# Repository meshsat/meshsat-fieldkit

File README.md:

# MeshSat Field Kit hardware

Hardware for the MeshSat field kits, the portable go-boxes that carry a MeshSat Bridge (a Raspberry Pi 5 in V1, three Compute Module 5 in V2) with its radios, satellite modem, cellular modem, GPS and power into the field. Since October 2026 it also holds the compact kit, the pocket-sized node (`compact/`). The software lives in the [meshsat](https://github.com/meshsat/meshsat) repository. This repository holds the mechanical and electronic design, the build records and the manufacturing files.

MeshSat is a prototype. Nothing here has been through a field deployment yet. The V1 kits are bench and demo units. The V2 boards are designed and generated, and the engineering foundations beneath them are still being completed: no V2 board is ready for layout, no layout of boards A, B, C, D, E or P carries its board's corrected schematic (E5 has none), and none has been fabricated or ordered ([`v2/docs/CURRENT-EVIDENCE.md`](v2/docs/CURRENT-EVIDENCE.md): "Foundations incomplete; 0 boards ready for layout; 0 physically verified").

## Latest: compact v2, the pocket-sized node in a printed enclosure (6 October 2026)

<sub>The compact v2 enclosure exploded, as designed (an OpenSCAD render; nothing printed). From the bottom: the belt plate, the body with the SOS guard and the LoRa antenna, the RockBLOCK 9704-SMA on its rails, the printed separator, the T-Beam Supreme with its 18650 cell, the lid with the OLED window; to the side, the TPU button membrane, the three plungers and their retainer.</sub>

The compact kit is the small MeshSat node: a Meshtastic LoRa radio and an Iridium modem in a case that fits a pocket, running the MeshSat fork of the Meshtastic firmware and talking to the MeshSat phone apps over one Bluetooth link. Its third version, **compact v2**, puts a LILYGO T-Beam Supreme over a RockBLOCK 9704-SMA in a 3D-printed stacked enclosure: ASA body, lid, separator and carry plates, a TPU membrane over the board's three side buttons, an O-ring cord seal, a polycarbonate pane over the OLED, two SMA bulkheads, an IP67 panel USB-C, an M12 vent and a 12 mm IP67 switch under a guard; 62.5 x 146.0 x 62.7 mm, 154.0 mm long with the SOS guard. The design is `meshsat-enclosure` v0.6 of 5 October 2026, the answer to an engineering audit of its v0.5: both boards are registered from the makers' STEP models, every printed part is clash-checked against them, and three test coupons (the 9704 rail slot, the rim with its seal and inserts, the upper bay with the real board) come before any full print. [`compact/`](compact/README.md) holds the version table for compact v0, v1 and v2; [`compact/v2/`](compact/v2/README.md) the source, the print files, the coupons, the renders and the validation chain.

State: designed, and cleared by its own audit response for prototype printing only. The first test coupons are being printed in October 2026; nothing has been printed, fitted or sealed. Open before a full build: the panel part numbers, how the 9704 is powered, Ground Control's certification condition on other transmitters in the same housing, and the leak, button and insert tests ([`compact/v2/AUDIT-RESPONSE.md`](compact/v2/AUDIT-RESPONSE.md)). Firmware, wiring and the Bluetooth contract: [meshsat-esp32](https://github.com/meshsat/meshsat-esp32), [meshsat-firmware](https://github.com/meshsat/meshsat-firmware) and [docs.meshsat.net/node/](https://docs.meshsat.net/node/).

## News

| Date | What |
|---|---|
| 6 October 2026 | The compact kit joins this repository as [`compact/`](compact/README.md): the version table for compact v0, v1 and v2, and the v2 enclosure package (OpenSCAD source, print STLs, test coupons, renders, validation chain, the makers' reference CAD). The first test coupons are being printed. |
| 5 October 2026 | The v2 enclosure reaches v0.6, the response to an engineering audit of v0.5 (findings F01 to F15, [`compact/v2/AUDIT-RESPONSE.md`](compact/v2/AUDIT-RESPONSE.md)): boards registered from the makers' STEP models, every printed part clash-checked, grounded test coupons in place of a floating fit check, a membrane and guided plungers for the side buttons. |
| 4 October 2026 | The V2 programme adopts an execution constitution ([`v2/docs/EXECUTION-CONSTITUTION.md`](v2/docs/EXECUTION-CONSTITUTION.md)): layer deliverables with explicit dependencies, independent checking, one freeze per candidate, and separate statements of handover readiness, power-design closure and fabrication release. |
| 3 October 2026 | A panel controller firmware for board C ([`v2/firmware/panel/`](v2/firmware/panel/README.md)): a portable core with its hardware layer, a pico-sdk port and host tests. The supplier engineering-handover entry page ([`v2/docs/handover/supplier/`](v2/docs/handover/supplier/)) with a per-board BOM reader from the committed netlists. Desk work: no board exists. |
| 27 September 2026 | The case set for the Peli 1450 ([`v2/release/case-2026-09-27/`](v2/release/case-2026-09-27/README.md)): face plate, RF entry plates, connector plate, frame legs and the lid tray as CAD, drawings and 1:1 templates. Nothing cut or fitted. |
| 26 September 2026 | Circuit corrections in the schematics of boards A, B, C, D, E and P. No committed layout carries them; the deliverable folders of `v2/release/revA/` predate them. |
| 7 September 2026 | The MESHSAT-830 generation: the Peli 1450 go-box around three Compute Module 5 slots, its boards generated from their generators (the V2 section below). |
| 3 September 2026 | This repository opens with the Rev A design release (`revA`) of the previous board generation (one compute module, the Touch Display, a twelve-cell battery module), kept on the GitHub release as the record. |
| April 2026 | The V1 kits tesseract and parallax built, in use since as bench and demo units ([`v1/`](v1/README.md)). |

## Folders

| Folder | What it is | State |
|---|---|---|
| `v1/` | tesseract and parallax as built: IP67 case, HDPE plates on M3 rods, UV-K5 + AIOC APRS chain, per-kit BOM and GPIO pinouts, FreeCAD plate model | built April 2026, in use |
| `v2/` | the Peli 1450 go-box of the MESHSAT-830 generation: seven carrier PCBs around three Compute Module 5 slots, an aluminium control face on the 1450PF panel frame with a sealed monitor in it and a backer board under it, a removable stack on a floor dock, a 4S pack built for the kit (about 145 Wh) in the east pocket | first generated 7 September 2026; circuits corrected on 26 September 2026 in the schematics only; foundations incomplete, 0 boards ready for layout, nothing built or ordered |
| `compact/` | the compact kit, the pocket-sized node: the version table for v0 (XIAO ESP32-S3 + Wio-SX1262 + RockBLOCK 9603 bench unit), v1 (LILYGO T-Beam Supreme + RockBLOCK 9603 for a Peli 1020) and v2 (T-Beam Supreme over a RockBLOCK 9704-SMA in a 3D-printed stacked enclosure, OpenSCAD, in `compact/v2/`) | v0 and v1 are bench units running since September 2026 (the v1 Peli build is not finished); v2 designed 5 October 2026, cleared by its own audit response for prototype printing only, nothing printed or fitted |

## V1: tesseract and parallax

Two hand-built kits that differ only in the satellite modem (tesseract: RockBLOCK 9603 SBD, parallax: RockBLOCK 9704 IMT). Pi 5 with a Geekworm X1202 UPS, LilyGO T-Call A7670E, u-blox GPS, Quansheng UV-K5(8) with an AIOC for APRS, ESP32-S3 LoRa for Meshtastic, RTL-SDR v4, ZigBee CC2652P, DCF77 receiver, WeAct 3.7 inch e-paper, Raspberry Pi Touch Display 2, all on three HDPE plates in an IP67 case with SMA bulkheads. Details, BOM and pinouts in [`v1/README.md`](v1/README.md). **To build one: [`v1/BUILD.md`](v1/BUILD.md)** (parts, case drilling, plates, harness tables, software provisioning, checks).

## V2: the carrier set (MESHSAT-830 generation, 7 September 2026)

Seven KiCad 9 boards replace the plates, the loose wiring and the USB hub. Three Raspberry Pi Compute Module 5 sit in identical slots on one carrier, each with a PCIe switch, an NVMe drive, a USB 3 hub and a card slot; most radios and the sensor and panel controllers are USB devices on those hubs, shared by the HAL across the three modules, which run k3s; each of the three hub banks is designed to switch in hardware from its home module to a neighbour, decided by three I/O supervisors voting two of three, so losing a module is meant to move its USB peripherals instead of removing them. Not everything is on a hub: the two WiFi link cards are PCIe cards on two different modules, and only their antennas move; the compute modules' own WiFi and Bluetooth stay with each module; and two bearers have no second path and go with their module, the LoRa module on one module's SPI and the 5G data path on another's PCIe lane ([`v2/docs/ARCH-PCB-B-IOHA.md`](v2/docs/ARCH-PCB-B-IOHA.md) section 15). The stack (PCB-A power with the VHF mezzanine, PCB-B compute) lifts straight out of the case, and a dock strip on the case floor carries the 9 to 36 V front end, the solar tracker, the sensor controller and the contact block that the stack lands on; as generated, eleven antenna paths blind-mate at the same time (a twelfth, the third 5G jack, waits on the board E clamp fit under owner ruling D-07). The face is a 3 mm aluminium plate on the Peli 1450PF frame (over Peli's o-ring, case choice C1) with a Xenarc IP67 monitor set into it, a wide-temperature e-paper under a lens, sealed switches, two headset jacks and a camera window, with the backer board C7 (an RP2040 panel controller) under it and the 30 W VHF amplifier bolted to its underside. The pack is a 4S lithium-ion pack, built rather than bought, for the pocket beside A24 at the east wall (the BB-2590/U did not fit the case; appendix 32.62). On 26 September 2026 the owner ruled its size: one 4S3P block of Samsung INR18650-35E cells, about 145 Wh, shrink-wrapped in that pocket, its fit designed against Peli's own figures ([`v2/docs/CASE-MARGINS.md`](v2/docs/CASE-MARGINS.md)), with missions longer than the pack relying on vehicle or solar input. The product brief, the concept of operations with its PROVISIONAL runtime per power state, the device set and the qualification plan are in [`v2/docs/PRODUCT-BRIEF.md`](v2/docs/PRODUCT-BRIEF.md), [`v2/docs/CONOPS.md`](v2/docs/CONOPS.md), [`v2/docs/V2-SPEC.md`](v2/docs/V2-SPEC.md) and [`v2/docs/TEST-PLAN.md`](v2/docs/TEST-PLAN.md); none of it has been built. Against Peli's own figures, the antenna entries are twelve gas-discharge arrestors on one RF entry plate per end wall at 59 mm and the wall items share one connector plate between the hinge fairings, choices the design session took under the owner's standing rule of 26 September 2026 ([`v2/docs/CASE-MARGINS.md`](v2/docs/CASE-MARGINS.md) section 4); the case generators carry them since `c351115d` and the current case set, CAD, drawings and 1:1 templates, is [`v2/release/case-2026-09-27/`](v2/release/case-2026-09-27/README.md), while the committed board files and the deliverable folders of `v2/release/revA/` predate it.

| Board | Rev (newest deliverable folder) | Declared phase | Size (mm) | Layers | Role |
|---|---|---|---|---|---|
| PCB-A POWER + I/O | A24 | A32 | 240 x 160 | 6 | the 14.4 V node from the 4S pack, BQ25731 SMBus charger, three 5.1 V slot rails and a device rail, the 13.8 V amplifier rail and the 12 V HF rail (both EMCON gated), the 54 V PoE rail, the 45 W USB-C outlet, INA226 rail monitors, the D8 mezzanine site, eleven blind-mate RF receptacles, the dock contacts |
| PCB-B COMPUTE | B19 (quote only, not routed) | B21 | 330 x 200 | 6 (an 8-layer trial ruled 25 Sep 2026) | three Compute Module 5 slots on board-to-board receptacles, per slot a PCIe switch with an NVMe 2242 and a card slot (a WiFi link card, the 5G module, the second WiFi link card), a four-port USB 3 hub and a cooler fan; the KSZ9897 Ethernet switch to the wall port with PoE, the three-input HDMI switch to the monitor, the LimeSDR bay, the RockBLOCK site, the LG290P GNSS, the E22 1 W LoRa module, two E72 radios (Zigbee and Thread), the holdover clock, the secure element, the panel ribbon |
| PCB-C PANEL BACKER | C24 | C24 | 344 x 228 ring | 4 (6 ruled 25 Sep 2026, not yet regenerated) | the ring under the face plate: the RP2040 panel controller (a USB device with the hardware EMCON and ZEROIZE lines), the sixteen LEDs under IP68 light guides (and, in the schematic since its round 8, a seventeenth, the hardware EMCON lamp, whose light guide in the plate is owed), two GPIO expanders, the e-paper flex socket and its boost stage, the sounder driver, the ambient light sensor, the lands for the sealed switches, the holes for the headset jacks and the monitor's connector block |
| PCB-D VHF APRS | D11 | D12 | 100 x 80 | 4 | the NiceRF SA868 exciter, the T/R relay, the low-pass filter and the leads to the RA30H1317M1 30 W module on the plate, a USB audio codec and headphone amplifier for the two headset jacks, a USB hub and the control bridge, the PTT and EMCON logic, the amplifier gate bias switch |
| PCB-E1 DOCK STRIP | E9 | E17 | 267 x 68 | 4 | the floor strip: 9 to 36 V vehicle and shore entry with the LM5176 front end, the solar tracker, the pack entry with its fuse and SMBus, the sensor controller (a second RP2040) with the climate, seal, water, gas, motion, lightning, Geiger and outside-pod inputs, two mixer fans, one blind-mate clamp bar with twelve cavities (board A's eleven RF sites and the third 5G jack of owner ruling D-07), the raised contact block |
| PCB-E5 DOCK BLOCK | E5 | E5 (no schematic) | 43 x 26 | 2 | the raised block on the strip: the targets the stack's spring pins land on, wire lands underneath |
| PCB-P PACK BMS | P4 | P4 | 70 x 44 | 2 (4 at 2 oz ruled 25 Sep 2026, not yet regenerated) | inside the 4S pack: the BQ4050 SMBus gauge with protection and balancing, two high-side N-FETs, the 2 mohm shunt, the 25 A blade, the cell tap, thermistor and SMBus headers, the lead lands (appendix 32.62) |

The revision column names the newest deliverable folder in `v2/release/revA/boards/`, and the declared phase is the board this project is building ([`v2/docs/CURRENT-EVIDENCE.md`](v2/docs/CURRENT-EVIDENCE.md)). Every deliverable folder predates the circuit corrections of 26 September 2026 (`faf8c981`, `458b2873`, `d90f30e4`) and every later one, which are in the schematics only: no layout of boards A, B, C, D, E or P carries its board's corrected netlist (E5 has no schematic). The renders below show those older layouts.

**Reading this page inside an engineering handover snapshot** (`v2/release/handover/<version>.zip`): the snapshot leaves out `v2/images/` (renders, presentation) and `v1/` (the V1 kits, out of the V2 handover's scope), so the images below and the links into `v1/` do not resolve there; they do in this repository. The snapshot's `EXCLUDED.tsv` lists every file left out, and its `START-HERE.md` section 7 says why.

| | |
|---|---|
|  |  |
| PCB-A POWER + I/O | PCB-B COMPUTE |
|  |  |
| PCB-C PANEL BACKER | PCB-D VHF APRS |
|  |  |
| PCB-E1 DOCK STRIP | PCB-E5 DOCK BLOCK |
|  | |
| PCB-P PACK BMS | |

Concept renders of the assembled kit as designed (not built; `v2/cad/render/` holds the Blender scene, `v2/images/concept-1450/README.md` the full set):

| | |
|---|---|
|  |  |
| the open case from the front | the face from above |
|  |  |
| the front wall cut away and the face lifted | the stack without the face |
|  |  |
| the switch corner | closed for transport |

**The V2 build guide, [`v2/BUILD.md`](v2/BUILD.md), is the 7 September generation's guide, kept as the assembly narrative and not to be used to order boards:** no board is ready for layout, and the order folder is rebuilt and quarantined with nothing ordered from it (owner decision 41 of 25 September 2026). Sources, generators, vendor references, the release and the order record are described in [`v2/README.md`](v2/README.md). The design record is [`v2/docs/MESHSAT-709-geometry-appendix.md`](v2/docs/MESHSAT-709-geometry-appendix.md), the build procedure [`v2/docs/ASSEMBLY.md`](v2/docs/ASSEMBLY.md), the panel controller contract [`v2/docs/PANEL.md`](v2/docs/PANEL.md).

## How to build one

| | Guide | What it covers |
|---|---|---|
| V1 | [`v1/BUILD.md`](v1/BUILD.md) | the 33-line parts list per kit, bulkhead and hole schedule, the three HDPE plates and the rod stack, what goes on which floor, the GPIO harness tables for both kits as wired, the Pi 5 provisioning sequence and its traps, the checks that prove the kit works |
| V2 | [`v2/BUILD.md`](v2/BUILD.md) | the 7 September generation's guide, headed as history and not for ordering (decision 41; 0 boards ready for layout): the boards as generated, everything else to buy, case and frame preparation, the 4S pack, the assembly order with torques, leads and pigtails, coating and labels, software bring-up, the open items, with the lines that contradict the current baseline corrected in place |

## Working with this repository

- Binaries (STEP, FreeCAD, DXF, zips, PDFs, renders) are ordinary git objects; a clone is about 400 MB and needs no Git LFS.
- KiCad 9, Freerouting and the generator scripts run headless on a rented build host; see `v2/README.md` for the pipeline and the prerequisites.
- `v2/vendor/` holds third-party reference material (manufacturer CAD, datasheets) under the vendors' own terms; see `v2/vendor/README.md`.

## Mission and use policy

MeshSat does not work with any organisation that develops, produces, integrates or operates weapon systems, and provides nothing for use in one. The licence below is unchanged: the policy covers whom we work with, not what you may do with the code. Read the [MeshSat Mission and Use Policy](https://meshsat.net/policy/).

## Licence

The hardware design, documentation and generator scripts in this repository are released under the CERN Open Hardware Licence Version 2, Strongly Reciprocal (CERN-OHL-S-2.0), see [`LICENSE`](LICENSE). Third-party files under `v2/vendor/` are not covered by it.

## Links

- Project site: [meshsat.net](https://meshsat.net)
- Bridge software: [github.com/meshsat/meshsat](https://github.com/meshsat/meshsat)
- This repository on GitHub: [github.com/meshsat/meshsat-fieldkit](https://github.com/meshsat/meshsat-fieldkit) (mirror of the GitLab original)

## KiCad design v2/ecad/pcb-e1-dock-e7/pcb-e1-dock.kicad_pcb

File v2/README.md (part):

# V2: the Peli 1450 carrier set (MESHSAT-830 generation)

Seven KiCad 9 boards for the kit V2 go-box: a Peli 1450 case with the 1450PF panel frame. The power and compute boards stack on four M3 rods and lift out of the case in one piece; a dock strip on the case floor carries the 9 to 36 V front end, the solar tracker, the sensor controller and the raised contact block that the stack blind-mates onto, with eleven antenna paths mating at the same time as generated (twelve with the third 5G jack of owner ruling D-07, which waits on the board E clamp fit). The control face is a 3 mm aluminium plate on top of the frame, over Peli's o-ring and screwed into Peli's inserts (`cad/face_plate.py`, `release/case-2026-09-27/face-plate/`; the session's case choice C1 of `docs/CASE-MARGINS.md` section 4, which the case generators carry since `c351115d`) with a Xenarc 709GNK monitor set into it, its glass level with the aluminium face (owner ruling of 9 September 2026, appendix 32.85), the backer board C7 hanging under it and the 30 W VHF module bolted to its underside; the 4S pack, built for the kit rather than bought (one 4S3P block of about 145 Wh by the owner's ruling of 26 September 2026, its fit designed against Peli's own figures, `docs/CASE-MARGINS.md`), lies in the pocket at the east end wall (appendix 32.62), and the antenna entries are twelve gas-discharge arrestors on one RF entry plate per end wall at 59 mm (case choices C2 and C4, carried by the case generators and the case set `release/case-2026-09-27/` since `c351115d`; the committed board files and the deliverable folders of `release/revA/` predate them). Nothing here has been built: the boards are designed and generated, no board is ready for layout (`docs/CURRENT-EVIDENCE.md`: "Foundations incomplete; 0 boards ready for layout; 0 physically verified"), and no set has been ordered.

The rulings that bind the design (details in `docs/MESHSAT-709-geometry-appendix.md`, sections 32.49 to 32.61, and the specification `docs/V2-SPEC.md`): three identical Compute Module 5 slots with most radios and the sensor and panel controllers USB devices shared by the HAL, k3s across the modules, and each hub bank switchable in hardware between its home module and a neighbour so one module's loss is meant to move its USB peripherals rather than remove them; the two WiFi link cards are PCIe cards on two modules whose antennas, not the cards, move, the compute modules' own radios stay with each module, and the LoRa module (one module's SPI) and the 5G data path (another's PCIe lane) have no second path and go with their module (`docs/ARCH-PCB-B-IOHA.md` section 15); the pack, the charger and the power control on PCB-A; no vent opening anywhere in the case; EMCON a hardware line from the panel toggle, plus a software hold, meant to silence every transmitter, with the radios dark and only the VHF receiver, GNSS, DCF77 and the lightning sensor still listening (the owner's ruling of 26 September 2026): as generated at `45bde541` it is drawn to remove the supply of the SDR, the RockBLOCK, the LoRa module, both Zigbee and Thread radios, the HF unit and both WiFi link cards, to turn off the amplifier's rail and keying while the VHF exciter keeps receiving, to pull the compute modules' own WiFi and Bluetooth disables low, and to put the 5G module in airplane mode through its disable pin, and since board B's round 8 (27 September 2026) it also removes the 5G module's supply by hardware at once (SD-EMC-1r8; `docs/CONOPS.md` section 4b, `docs/feasibility/EMCON.md` section 4b); read transmitter by transmitter (`docs/feasibility/EMCON.md` section 0a) none of the kit's 17 transmitters is dark end to end: the radio's own chain closes at desk for 15 and is open for the SA868 (its PTT pin's receive threshold is unpublished) and the RockBLOCK 9704 (once its supply is cut it runs on its own supercapacitors with its ENABLE held by firmware, so the ENABLE forced low by the EMCON hardware is owed); every row also waits on the items the rows share (the toggle and its conductor, whose hardware EMCON lamp is drawn on board C since its round 8 with its light guide in the plate owed) and on the latency the session set (1 s, 20 s for a running 5G module; REQ-071), and no row has been shown on a bench (feasibility blocker FEA-002); the panel a USB device driven per `docs/PANEL.md`.

| Board | Rev (newest deliverable folder) | Declared phase | Size (mm) | Layers | Project | Deliverable folder |
|---|---|---|---|---|---|---|
| PCB-A POWER + I/O | A24 | A32 | 240 x 160 | 6 | `ecad/pcb-a-power-a23/` | `release/revA/boards/meshsat-pcb-a-revA-A24/` |
| PCB-B COMPUTE | B19 | B21 | 330 x 200 | 6 (8-layer trial ruled 25 Sep 2026) | `ecad/pcb-b-compute-b19/` | `release/revA/boards/meshsat-pcb-b-revA-B19-quote/` (quote only: placed, not routed) |
| PCB-C PANEL BACKER | C24 | C24 | 344 x 228 ring | 4 (6 ruled 25 Sep 2026, not yet regenerated) | `ecad/pcb-c-display-c8/` | `release/revA/boards/meshsat-pcb-c-revA-C24/` |
| PCB-D VHF APRS | D11 | D12 | 100 x 80 | 4 | `ecad/pcb-d-aprs-d9/` | `release/revA/boards/meshsat-pcb-d-revA-D11/` |
| PCB-E1 DOCK STRIP | E9 | E17 | 267 x 68 | 4 | `ecad/pcb-e1-dock-e7/` | `release/revA/boards/meshsat-pcb-e-revA-E9/` |
| PCB-E5 DOCK BLOCK | E5 | E5 (no schematic) | 43 x 26 | 2 | `ecad/pcb-e5-block/` | `release/revA/boards/meshsat-pcb-e5-revA-E5/` |
| PCB-P PACK BMS | P4 | P4 | 70 x 44 | 2 (2 oz; 4 at 2 oz ruled 25 Sep 2026, not yet regenerated) | `ecad/pcb-p-pack-p2/` | `release/revA/boards/meshsat-pcb-p-revA-P4/` |

Every deliverable folder in this table predates the circuit corrections of 26 September 2026 (`faf8c981`, `458b2873`, `d90f30e4`) and every later one, which are in the schematics only: no layout of boards A, B, C, D, E or P carries its board's corrected netlist (SCH-002 reads FAIL on A and B and INCONCLUSIVE on C, D, E and P; E5 has no schematic, and its board file is its design), and each board's remaining layout-entry blockers are listed in `docs/CURRENT-EVIDENCE.md`.

The previous generation (A21, B15, C6, D7, E4, E5 with a single Compute Module, the Touch Display and a twelve-cell battery module) stays on the `revA` GitHub release and in the git history as the record; its deliverable folders are replaced as the new boards land.

**Build guide: [`BUILD.md`](BUILD.md)** is the 7 September generation's guide, kept as the assembly narrative and headed as not for ordering (owner decision 41; no board is ready for layout). This page is the map of the folder.

## Layout

| Path | Content |
|---|---|
| `docs/` | `MESHSAT-709-geometry-appendix.md` (the design record, every number and every ruling), `ASSEMBLY.md` (fasteners, torque, coating, removal procedure, bench-fit lists), `PANEL.md` (the software contract for the control panel, MESHSAT-773), `V2-SPEC.md` (the approved specification of the next generation, MESHSAT-830, with its corrections of 26 September 2026), `TEST-PLAN.md` (its qualification plan), `PRODUCT-BRIEF.md` and `CONOPS.md` (the product brief and the concept of operations of the foundation baseline, MESHSAT-1357), `CURRENT-EVIDENCE.md` (what each board's evidence shows today), `CASE-MARGINS.md` (the case held against Peli's own figures, with the case choices C1 to C6), `ARCHITECTURE.md` and `feasibility/` (the architecture and the feasibility of the core functions), `EXECUTION-PLAN.md` (the foundation programme and its stage gates), `records/` (the session records the pages cite) and `reviews/` (the owner's reviews and prompts) |
| `ecad/` | the KiCad sources: one project folder per board, `meshsat.pretty/` (project footprints), `tools/` (the generators and the pipeline scripts) |
| `vendor/` | third-party reference CAD and datasheets (see `vendor/README.md`) |
| `release/revA/boards/` | the Rev A deliverables: KiCad project snapshot, Gerber zip, BOM, CPL, DRC report, schematic PDF, renders, 1:1 print |
| `release/revA/order/` | the JLCPCB order set: per-board upload folder with `ORDER-NOTES.txt`, `ORDER-LOG.md` (what was uploaded and what JLCPCB answered), `jlc-rotations.csv` and `jlc_final.py` (the rotation fixes applied to the CPL) |
| `release/revA/review/` | the review prints: 1:1 sheets, assembly drawings, copper layers, schematics, renders at A4 |
| `images/` | downscaled top renders for the README (left out of the engineering handover snapshots under `release/handover/`, as presentation, so the README's image links do not resolve inside a snapshot; they do in this repository) |

## State of the MESHSAT-830 generation

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
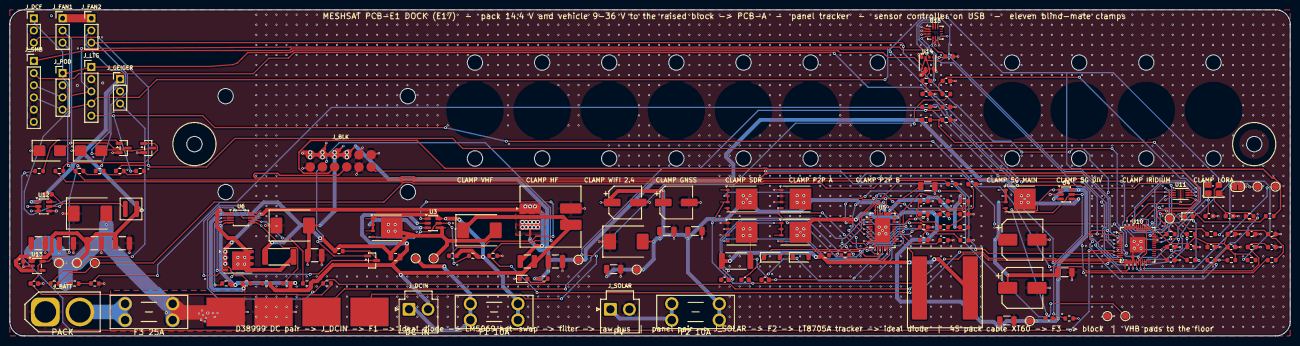
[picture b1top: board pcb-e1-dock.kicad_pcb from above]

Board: 4 copper layers, 267.0 x 68.0 mm, 189 parts (0 on the bottom side), 94 nets.

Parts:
C1, C31: 10u 25V 1210; C_1210_3225Metric
C2: 100n 100V; C_0805_2012Metric
C4, C28: 100n 50V; C_0603_1608Metric
C5: 100n (TIMER); C_0603_1608Metric
C6: 1u 100V 1210 (X, input side); C_1210_3225Metric
C7: 1u 100V 1210 (X, bus side); C_1210_3225Metric
C8: 10u 100V X7R 1210; C_1210_3225Metric
C11, C12: 100u 35V Panasonic EEHZK1V101XP hybrid polymer (7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; CP_Elec_6.3x7.7
C13, C14: 10u 50V; C_1206_3216Metric
C15: 4.7u 50V; C_1206_3216Metric
C16: 1n; C_0603_1608Metric
C17, C18: 470n 25V; C_0603_1608Metric
C19: 4.7u 25V; C_1206_3216Metric
C20, C34, C35, C45, C46, C47: 1u; C_0603_1608Metric
C21: 4.7n; C_0603_1608Metric
C22: 100p; C_0603_1608Metric
C23, C30, C38, C39, C40, C41, C42, C43, C44, C48, C49, C50, C51: 100n; C_0603_1608Metric
C24, C25: 39u 35V Panasonic 35SVPF39M polymer (6.9 mm); CP_Elec_8x6.7
C26, C27: 10u 25V; C_1206_3216Metric
C32, C33: 22u 10V X7R 1210; C_1210_3225Metric
C36, C37: 15p; C_0603_1608Metric
D1: SMCJ40A (input surge: 40 V standoff on a line spe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; D_SMC
D2: SMCJ40A (bus clamp: 40 V standoff on the 9 to 36 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; D_SMC
D3: SMCJ18A (pack node clamp); D_SMC
D4: SMCJ28A (panel surge: 28 V standoff, conducting f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; D_SMC
D5: BAT54 boost diode INTVCC -> BOOST1; D_SOD-123
D6: BAT54 boost diode INTVCC -> BOOST2; D_SOD-123
D7: SS14 flyback across fan 1; D_SMB
D8: SS14 flyback across fan 2; D_SMB
F1: 10 A mini blade (Keystone 3568 holder): vehicle i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; Fuseholder_Blade_Mini_Keystone_3568
F2: 10 A mini blade (Keystone 3568 holder): panel inp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; Fuseholder_Blade_Mini_Keystone_3568
F3: 25 A mini blade (Keystone 3568 holder): pack to t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; Fuseholder_Blade_Mini_Keystone_3568
H1, H2: M3 rod pass-through, PCB-A standoff stands here; MountingHole_3.2mm_M3
H3, H4, H5, H6: M3 standoff, raised block; MountingHole_3.2mm_M3
H7, H8: M3, float clamp VHF; MountingHole_3.2mm_M3
H9, H10: M3, float clamp HF; MountingHole_3.2mm_M3
H11, H12: M3, float clamp WIFI 2.4; MountingHole_3.2mm_M3
H13, H14: M3, float clamp GNSS; MountingHole_3.2mm_M3
H15, H16: M3, float clamp SDR; MountingHole_3.2mm_M3
H17, H18: M3, float clamp P2P A; MountingHole_3.2mm_M3
H19, H20: M3, float clamp P2P B; MountingHole_3.2mm_M3
H21, H22: M3, float clamp 5G MAIN; MountingHole_3.2mm_M3
H23, H24: M3, float clamp 5G DIV; MountingHole_3.2mm_M3
H25, H26: M3, float clamp IRIDIUM; MountingHole_3.2mm_M3
H27, H28: M3, float clamp LORA; MountingHole_3.2mm_M3
JP1: BOOTSEL: short while powering to enter the USB bo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; SolderJumper-2_P1.3mm_Open_RoundedPad1.0x1.5mm
J_BATT: Amass XT60-M: the BB-2590/U pack cable BTA-70762-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; AMASS_XT60-M_1x02_P7.20mm_Vertical
J_BLK: solder lands for the 12 signal wires to the block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; PogoTargets_2x6
J_DCF: DCF77 receiver module: 3.3 V, GND, pulse; PinHeader_1x03_P2.54mm_Vertical
J_DCIN: JST-VH socket, 10 A: vehicle and shore DC in 9 to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; JST_VH_B2P-VH_1x02_P3.96mm_Vertical
J_FAN1: mixer fan 1 under the plate (12 V class fan on th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; PinHeader_1x03_P2.54mm_Vertical
J_FAN2: mixer fan 2 under the plate (12 V class fan on th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; PinHeader_1x03_P2.54mm_Vertical
J_GEIGER: Geiger counter module (RadiationD-v1.1 class): 5 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; PinHeader_1x03_P2.54mm_Vertical
J_LTG: AS3935 lightning sensor module (CJMCU-3935 class)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; PinHeader_1x05_P2.54mm_Vertical
J_POD: outside sensor pod on the connector plate (M8 sea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; PinHeader_1x04_P2.54mm_Vertical
J_SMB: pack SMBus (XH or pin header): section A SDA SCL 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; PinHeader_1x06_P2.54mm_Vertical
J_SOLAR: JST-VH socket, 10 A: bare panel in (lead from the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; JST_VH_B2P-VH_1x02_P3.96mm_Vertical
L1: 10uH Coilcraft XAL1510-103MED (Isat 26 A, 10.0 mm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; L_Coilcraft_XAL1510-103
L2: Bourns SRF1260-4R7Y dual-winding choke (7.2 A per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; L_CommonModeChoke_Bourns_SRF1260
L3: 4.7uH XAL4030-472ME; L_Coilcraft_XAL4020-XXX
LED1: green: vehicle input present; LED_0603_1608Metric
LED2: status (GPIO25); LED_0603_1608Metric
PAD_W1: water electrode A (bare copper, +3.3 V through 1 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; SolderPad_8x6
PAD_W2: water electrode B (bare copper, to ADC0); SolderPad_8x6
P_CN: solder pad, 12 AWG wire to the block board return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; SolderPad_8x6
P_CP: solder pad, 12 AWG wire to the block board CELL+ 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; SolderPad_8x6
Q1, Q2: BSC039N06NS 60 V 3.9 mOhm N-FET (PG-TDSON-8: 1-3 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; TDSON-8-1
Q3: BSC028N06NS 60 V 2.8 mOhm N-FET, M1 buck top (TDS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; TDSON-8-1
Q4: BSC039N06NS 60 V N-FET, M2 buck bottom; TDSON-8-1
Q5: BSC028N06NS 60 V N-FET, M3 boost bottom; TDSON-8-1
Q6: BSC039N06NS 60 V N-FET, M4 boost top; TDSON-8-1
Q7: CSD19532Q5B 100 V N-FET (4.6 mOhm at VGS 6 V, Pow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; PowerPAK_SO-8_Single
Q8: 2N7002: SHORE_INHIBIT high pulls UVLO low = input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; SOT-23
Q9: 2N7002 fan 1 low-side switch (1 G, 2 S, 3 D); SOT-23
Q10: 2N7002 fan 2 low-side switch (1 G, 2 S, 3 D); SOT-23
R1, R18, R26: 100k; R_0603_1608Metric
R5: 5 mOhm 1% 3 W 2512 RSENSE (RALEC LR2512-23R005F4); R_2512_6332Metric
R6, R7, R44, R45: 100R; R_0603_1608Metric
R8: 102k 1% (RFBIN1: panel point 17.6 V); R_0603_1608Metric
R9: 7.50k 1% (RFBIN2); R_0603_1608Metric
R10: 115k 1% (RFBOUT1: 15.1 V); R_0603_1608Metric
R11: 10.0k 1% (RFBOUT2); R_0603_1608Metric
R12: 215k 1% (RT: 202 kHz); R_0603_1608Metric
R13, R16, R17, R25, R31, R46, R47, R49, R50: 10k; R_0603_1608Metric
R14, R20, R22, R40, R42: 100k 1%; R_0603_1608Metric
R15: 15.0k 1% (SHDN: enable above about 9.5 V); R_0603_1608Metric
R19: 10mOhm 1% 2512 (hot-swap sense); R_2512_6332Metric
R21: 38.3k 1% (UVLO: 9 V); R_0603_1608Metric
R23: 6.65k 1% (OVLO: 40 V); R_0603_1608Metric
R24: 20k (PWR: power limit); R_0603_1608Metric
R27: 2.2k; R_0603_1608Metric
R28, R33: 1k; R_0603_1608Metric
R29, R30: 27R; R_0603_1608Metric
R32: 1k (BOOTSEL); R_0603_1608Metric
R34, R35, R36, R37: 4.7k; R_0603_1608Metric
R38, R39: 1M; R_0603_1608Metric
R41: 10k 1% (ADC1: 0.091 x bus); R_0603_1608Metric
R43: 22k 1% (ADC2: 0.18 x pack); R_0603_1608Metric
R48: 22R (pulse input series); R_0603_1608Metric
R51: 0R (CSB high: I2C mode; its own net keeps the pin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; R_0603_1608Metric
TP1: DC_IN; TestPoint_Pad_D1.5mm
TP2: DC_P; TestPoint_Pad_D1.5mm
TP3: VIN_RAW; TestPoint_Pad_D1.5mm
TP4: GND; TestPoint_Pad_D1.5mm
TP5: PV_P; TestPoint_Pad_D1.5mm
TP6: TRK_OUT; TestPoint_Pad_D1.5mm
TP7: BLK_SPARE; TestPoint_Pad_D1.5mm
TP8: CELL_F; TestPoint_Pad_D1.5mm
TP9: +5V_E6; TestPoint_Pad_D1.5mm
TP10: SWCLK; TestPoint_Pad_D1.5mm
TP11: SWDIO; TestPoint_Pad_D1.5mm
TP12: E6_RUN; TestPoint_Pad_D1.5mm
TP13: GEIGER_IN; TestPoint_Pad_D1.5mm
U3, U4: LM74700-Q1 ideal-diode controller: 1 VCAP 2 GND 3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; SOT-23-6
U5: LT8705A buck-boost controller, 38-lead QFN 5x7 (p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; WQFN-38-1EP_5x7mm_P0.5mm_EP3.15x5.15mm
U6: LM5069MM-2 hot-swap controller: 9 V on, 40 V off,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; VSSOP-10_3x3mm_P0.5mm
U10: RP2040 sensor controller (USB to B16 through the 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; QFN-56-1EP_7x7mm_P0.4mm_EP3.2x3.2mm
U11: W25Q16JVUXIQ 16 Mbit QSPI flash (USON-8: 1 CS 2 D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; Winbond_USON-8-1EP_3x2mm_P0.5mm_EP0.2x1.6mm
U12: AP63205WU-7 5 V 2 A buck for the controller, the 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; TSOT-23-6
U13: TLV75533PDBVR 3.3 V LDO; SOT-23-5
U14: BME688 inside climate: temperature, humidity, pre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; Bosch_LGA-8_3x3mm_P0.8mm_ClockwisePinNumbering
U15: BMI270 six-axis IMU (I2C 0x68): shock and tilt lo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; Bosch_LGA-14_3x2.5mm_P0.5mm
Y1: 12 MHz ABM8-272-T3 (3225): 1 XIN, 3 XOUT, 2 and 4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; Crystal_SMD_3225-4Pin_3.2x2.5mm

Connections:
/+3V3_E6: C35.1, C38.1, C39.1, C40.1, C41.1, C42.1, C43.1, C44.1, C47.1, C48.1, C49.1, C50.1, J_DCF.1, J_LTG.1, J_POD.1, R25.2, R31.2, R34.2, R35.2, R36.2, R37.2, R38.1, R46.2, R47.2, R49.2, R50.2, R51.1, U10.1, U10.10, U10.22, U10.33, U10.42, U10.43, U10.44, U10.48, U10.49, U11.8, U13.5, U14.2, U14.6, U14.8, U15.5, U15.8
/+5V_E6: C32.1, C33.1, C34.1, J_GEIGER.1, L3.2, TP9.1, U12.1, U13.1, U13.3
/BLK_SPARE: J_BLK.12, TP7.1
/BOOT_J: JP1.1, R32.2
/CELL+: F3.1, J_BATT.2
/CELL_F: C1.1, C31.1, D3.2, D7.1, D8.1, F3.2, J_FAN1.1, J_FAN2.1, P_CP.1, R42.1, TP8.1, U12.2, U12.3
/CELL_MON: R42.2, R43.1, U10.40
/DCF_PULSE: J_DCF.3, R49.1, U10.8
/DCIN_PGD: R25.1, U6.8, U10.15
/DC_F: C4.2, F1.2, Q1.1, Q1.2, Q1.3, R1.2, U3.3, U3.6
/DC_HS: C6.1, L2.1, Q7.1, Q7.2, Q7.3, U6.9
/DC_IN: F1.1, J_DCIN.1, TP1.1
/DC_P: C2.1, D1.2, Q1.5, R19.1, R20.1, R22.1, TP2.1, U3.4, U6.2
/E6_BST: C30.1, U12.6
/E6_DVDD: C45.1, C46.1, U10.23, U10.45, U10.50
/E6_RUN: R31.1, TP12.1, U10.26
/E6_SW: C30.2, L3.1, U12.5
/FAN1_G: Q9.1, R44.2
/FAN1_PWM: R44.1, U10.11
/FAN1_SW: D7.2, J_FAN1.2, Q9.3
/FAN1_TACH: J_FAN1.3, R46.1, U10.13
/FAN2_G: Q10.1, R45.2
/FAN2_PWM: R45.1, U10.12
/FAN2_SW: D8.2, J_FAN2.2, Q10.3
/FAN2_TACH: J_FAN2.3, R47.1, U10.14
/GEIGER_IN: R48.2, TP13.1, U10.9
/GEIGER_PULSE: J_GEIGER.3, R48.1
/GND_V: C2.2, C5.2, C6.2, D1.1, J_DCIN.2, L2.3, Q8.2, R21.2, R23.2, R24.2, U3.2, U6.5
/HS_GATE: Q7.4, U6.10
/HS_OVLO: R22.2, R23.1, U6.4
/HS_PWR: R24.1, U6.7
/HS_S: Q7.5, R19.2, U6.1
/HS_TIMER: C5.1, U6.6
/HS_UVLO: Q8.3, R20.2, R21.1, U6.3
/IMU_CSB: R51.2, U15.12
/IMU_INT1: U10.16, U15.4
/LED_A: LED1.2, R27.2
/LED_STAT: R33.1, U10.37
/LED_STAT_A: LED2.2, R33.2
/LTG_IRQ: J_LTG.5, R50.1, U10.17
/PV_IN: F2.1, J_SOLAR.1
/PV_P: C11.1, C12.1, C13.1, C14.1, C15.1, D4.2, F2.2, Q3.5, R8.1, R14.1, TP5.1, U5.32, U5.33, U5.34
/Q1_G: Q1.4, R1.1, U3.5
/Q2_G: Q2.4, R18.1, U4.5
/QSPI_D0: U10.53, U11.5
/QSPI_D1: U10.55, U11.2
/QSPI_D2: U10.54, U11.3
/QSPI_D3: U10.51, U11.7
/QSPI_SCLK: U10.52, U11.6
/QSPI_SS: R32.1, U10.56, U11.1
/SCL0: J_SMB.2, R35.1, U10.5
/SCL1: J_LTG.4, J_POD.4, J_SMB.4, R37.1, U10.7, U14.4, U15.13
/SDA0: J_SMB.1, R34.1, U10.4
/SDA1: J_LTG.3, J_POD.3, J_SMB.3, R36.1, U10.6, U14.3, U15.14
/SHORE_INHIBIT: J_BLK.8, Q8.1, R26.1, U10.18
/SWCLK: TP10.1, U10.24
/SWDIO: TP11.1, U10.25
/TRK_BG1: Q4.4, U5.14
/TRK_BG2: Q5.4, U5.16
/TRK_BOOST1: C17.1, D5.1, U5.23
/TRK_BOOST2: C18.1, D6.1, U5.17
/TRK_CSN: C16.2, R7.2, U5.2
/TRK_CSP: C16.1, R6.2, U5.3
/TRK_FBIN: R8.2, R9.1, U5.5
/TRK_FBOUT: R10.2, R11.1, U5.6
/TRK_IMONI: R16.1, U5.38
/TRK_IMONO: R17.1, U5.7
/TRK_INTVCC: C19.1, D5.2, D6.2, U5.15, U5.35, U5.36
/TRK_LDO33: C20.1, U5.4
/TRK_LSENSE: L1.2, R5.1, R6.1
/TRK_OUT: C24.1, C25.1, C26.1, C27.1, C28.2, Q2.1, Q2.2, Q2.3, Q6.5, R10.1, R18.2, TP6.1, U4.3, U4.6, U5.29, U5.30, U5.31
/TRK_RT: R12.1, U5.12
/TRK_SHDN: R14.2, R15.1, U5.1
/TRK_SS: C23.1, U5.9
/TRK_SW1: C17.2, L1.1, Q3.1, Q3.2, Q3.3, Q4.5, U5.21
/TRK_SW2: C18.2, Q5.5, Q6.1, Q6.2, Q6.3, R5.2, R7.1, U5.19
/TRK_TG1: Q3.4, U5.22
/TRK_TG2: Q6.4, U5.18
/TRK_VC: C22.1, R13.1, U5.8
/TRK_VCC1: C21.1, R13.2
/U3_VCAP: C4.1, U3.1
/U4_VCAP: C28.1, U4.1
/USB_DM_R: R30.1, U10.46
/USB_DP_R: R29.1, U10.47
/USB_E6_N: J_BLK.10, R30.2
/USB_E6_P: J_BLK.9, R29.2
/VIN_MON: R40.2, R41.1, U10.39
/VIN_RAW: C7.1, C8.1, D2.2, J_BLK.1, J_BLK.2, J_BLK.3, J_BLK.4, L2.2, Q2.5, R27.1, R40.1, TP3.1, U4.4
/WATER_A: PAD_W1.1, R38.2
/WATER_SENSE: C51.1, PAD_W2.1, R39.1, U10.38
/XIN: C36.1, U10.20, Y1.1
/XOUT: C37.1, R28.2, Y1.3
/XOUT_R: R28.1, U10.21
GND: C1.2, C7.2, C8.2, C11.2, C12.2, C13.2, C14.2, C15.2, C19.2, C20.2, C21.2, C22.2, C23.2, C24.2, C25.2, C26.2, C27.2, C31.2, C32.2, C33.2, C34.2, C35.2, C36.2, C37.2, C38.2, C39.2, C40.2, C41.2, C42.2, C43.2, C44.2, C45.2, C46.2, C47.2, C48.2, C49.2, C50.2, C51.2, D2.1, D3.1, D4.1, JP1.2, J_BATT.1, J_BLK.5, J_BLK.6, J_BLK.7, J_BLK.11, J_DCF.2, J_GEIGER.2, J_LTG.2, J_POD.2, J_SMB.5, J_SMB.6, J_SOLAR.2, L2.4, LED1.1, LED2.1, P_CN.1, Q4.1, Q4.2, Q4.3, Q5.1, Q5.2, Q5.3, Q9.2, Q10.2, R9.2, R11.2, R12.2, R15.2, R16.2, R17.2, R26.2, R39.2, R41.2, R43.2, TP4.1, U4.2, U5.11, U5.13, U5.37, U5.39, U10.19, U10.57, U11.4, U11.9, U12.4, U13.2, U14.1, U14.5, U14.7, U15.1, U15.2, U15.3, U15.6, U15.7, Y1.2, Y1.4

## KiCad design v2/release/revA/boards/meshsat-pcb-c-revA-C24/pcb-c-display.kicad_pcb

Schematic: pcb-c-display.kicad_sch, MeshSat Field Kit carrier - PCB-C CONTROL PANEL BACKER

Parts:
BZ1: IP67 panel-mount sounder, 5 V DC continuous, beze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; PanelSounder
C1, C2: 10u; C_0805_2012Metric; LCSC C15850
C3, C4, C14, C15, C16: 1u; C_0603_1608Metric
C5, C6: 15p NP0; C_0402_1005Metric
C7, C8, C9, C10, C11, C12, C13, C25, C29, C38: 100n; C_0603_1608Metric
C17, C18, C26, C27: 100n; C_0603_1608Metric; LCSC C14663
C19, C20, C21, C22, C23, C24: 10n; C_0603_1608Metric; LCSC C57112
C28: 4.7u; C_0805_2012Metric
C30, C31, C32, C33, C34, C35, C36, C37: 1u 25V; C_0603_1608Metric
CAM_H1, CAM_H2: M2 screw of the USB camera module (25 x 25 board,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; MountingHole_2.2mm_M2
D1: 3 mm MWARN red, sunlight viewable; LED_D3.0mm
D2: 3 mm MCAUT amber, sunlight viewable; LED_D3.0mm
D3: 3 mm TX red (RF hazard), sunlight viewable; LED_D3.0mm
D4: 3 mm SOSACT red, sunlight viewable; LED_D3.0mm
D5: 3 mm SAT green, sunlight viewable; LED_D3.0mm
D6: 3 mm MESH green, sunlight viewable; LED_D3.0mm
D7: 3 mm LTE green, sunlight viewable; LED_D3.0mm
D8: 3 mm GPS green, sunlight viewable; LED_D3.0mm
D9: 3 mm SHORE green, sunlight viewable; LED_D3.0mm
D10: 3 mm CHG white, sunlight viewable; LED_D3.0mm
D11: 3 mm MSG white, sunlight viewable; LED_D3.0mm
D12: 3 mm BAT1 amber, sunlight viewable; LED_D3.0mm
D13: 3 mm BAT2 green, sunlight viewable; LED_D3.0mm
D14: 3 mm BAT3 green, sunlight viewable; LED_D3.0mm
D15: 3 mm BAT4 green, sunlight viewable; LED_D3.0mm
D16: 3 mm BAT5 green, sunlight viewable; LED_D3.0mm
D17: BAT54 lamp-test tie; D_SOD-123; LCSC C7502705
D18: status (GPIO25); LED_0603_1608Metric
D19: SS2040FL: EPD_SW -> VGH; D_SOD-123F
D20: SS2040FL: pump clamp; D_SOD-123F
D21: SS2040FL: pump -> VGL; D_SOD-123F
FB1, FB2, FB3, FB4: ferrite 600R; L_0603_1608Metric; LCSC C1002
H1, H2, H3, H4, H5, H6, H7, H8: M3 x 6 into the face plate's self-clinching stand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; BackerScrew_M3_GND
JP1: BOOTSEL: short while powering to enter the USB bo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; SolderJumper-2_P1.3mm_Open_RoundedPad1.0x1.5mm
JP2: PANEL_ID strap (closed = variant B); SolderJumper-2_P1.3mm_Open_RoundedPad1.0x1.5mm
J_EPD: Hirose FH34SRJ-24S-0.5SH ZIF for the E2370KS0C1 f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; Hirose_FH34SRJ-24S
J_HSJ1: U-174/U headset jack 1 (Amphenol Nexus class, dra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; PanelJack_17mm
J_HSJ2: U-174/U headset jack 2 (Amphenol Nexus class, dra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; PanelJack_17mm
J_MAINSW: MAIN button lead to A22 J_MAINSW (XH2.5 at the A2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; LeadLands_1x02
J_PANEL: panel ribbon from B16 J_PANEL (IDC 2x13 SMD, unde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; IDC-Header_2x13_P2.54mm_Vertical_SMD
J_PIJ2: PI button lead: two solder lands on the underside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; LeadLands_1x02
L1: 10uH ATNR4010100MT 0.8 A (the boost inductor); L_APV_ANR4020
Q1: AO3401A P-FET high side; SOT-23; LCSC C15127
Q2, Q3, Q4: 2N7002; SOT-23; LCSC C8545
Q5: AO3401A P-FET: the e-paper's supply switch (EPD_P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; SOT-23; LCSC C15127
Q6: Si2302CDS-T1-GE3 logic-level N-FET (Vishay, SOT-2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; SOT-23; LCSC C10488
R1, R6: 1k; R_0603_1608Metric
R2, R3: 27R; R_0603_1608Metric
R4, R42: 10k; R_0603_1608Metric
R5: 1k (BOOTSEL); R_0603_1608Metric
R7, R8: 2.2k; R_0603_1608Metric
R9, R10, R11, R12, R13, R14, R15, R16: 10k; R_0603_1608Metric; LCSC C25804
R17: 2.2k; R_0603_1608Metric; LCSC C4190
R18: 47R; R_0603_1608Metric; LCSC C23182
R19, R44: 100R; R_0603_1608Metric; LCSC C22775
R20, R38, R45: 100k; R_0603_1608Metric; LCSC C25803
R21, R22, R23, R31, R36, R40: 300R; R_0603_1608Metric; LCSC C23025
R24, R25, R26, R27, R28, R29, R30, R32, R33, R34, R35: 180R; R_0603_1608Metric; LCSC C22828
R37: 1k; R_0603_1608Metric; LCSC C21190
R39, R41: 470R; R_0603_1608Metric; LCSC C23179
R43: 0.47R 1%; R_0603_1608Metric
SW_EMCON: EMCON locking toggle (closed = TX inhibit, a hard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; ToggleBody_SPDT
SW_LIGHT: LIGHTING DAY/NIGHT/BLACKOUT toggle DPDT ON-ON-ON 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; ToggleBody_DPDT
SW_MAIN: MAIN PWR 19 mm momentary, green ring (to A22 J_MA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; PanelSwitch_19mm
SW_PI: PI 16 mm recessed momentary, amber ring (PI_SHDN_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; PanelSwitch_16mm
SW_SOS: SOS locking toggle, maintained (APEM 5636ADKB-2V,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; ToggleBody_SPDT
SW_TEST: TEST/ACK 16 mm momentary, white ring; C&K ATP16-S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; PanelSwitch_16mm
SW_ZERO: ZEROIZE locking toggle, maintained (APEM 5636ADKB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; ToggleBody_SPDT
TP1: SWCLK; TestPoint_Pad_D1.5mm
TP2: SWDIO; TestPoint_Pad_D1.5mm
TP3: C_RUN; TestPoint_Pad_D1.5mm
TP4: LED_RAIL; TestPoint_Pad_D1.5mm
TP5: LED_RAIL_SW; TestPoint_Pad_D1.5mm
TP6: +5V; TestPoint_Pad_D1.5mm
TP7: +3V3; TestPoint_Pad_D1.5mm
TP8: GND; TestPoint_Pad_D1.5mm
TP9: EXP_INT; TestPoint_Pad_D1.5mm
TP10: TX_INHIBIT_n; TestPoint_Pad_D1.5mm
TP11: EMCON_HW; TestPoint_Pad_D1.5mm
TP12: ZEROIZE_HW; TestPoint_Pad_D1.5mm
TP13: SPARE1; TestPoint_Pad_D1.5mm
TP14: SPARE2; TestPoint_Pad_D1.5mm
TP15: SPARE3; TestPoint_Pad_D1.5mm
TP16: SPARE4; TestPoint_Pad_D1.5mm
TP17: SPARE5; TestPoint_Pad_D1.5mm
TP18: SPARE6; TestPoint_Pad_D1.5mm
TP19: SPARE7; TestPoint_Pad_D1.5mm
TP20: SPARE8; TestPoint_Pad_D1.5mm
TP21: SPARE9; TestPoint_Pad_D1.5mm
TP22: SPARE10; TestPoint_Pad_D1.5mm
TP23: SPARE11; TestPoint_Pad_D1.5mm
TP24: SPARE12; TestPoint_Pad_D1.5mm
TP25: EPD_BUSY; TestPoint_Pad_D1.5mm
TP26: EPD_VGH; TestPoint_Pad_D1.5mm
TP27: EPD_VGL; TestPoint_Pad_D1.5mm
TP28: HB1; TestPoint_Pad_D1.5mm
TP29: HB2; TestPoint_Pad_D1.5mm
TP30: HB3; TestPoint_Pad_D1.5mm
TP31: SLOT_EN1; TestPoint_Pad_D1.5mm
TP32: SLOT_EN2; TestPoint_Pad_D1.5mm
TP33: SLOT_EN3; TestPoint_Pad_D1.5mm
TP34: HDMI_SEL1; TestPoint_Pad_D1.5mm
TP35: HDMI_SEL2; TestPoint_Pad_D1.5mm
TP36: PI_SHDN_REQ; TestPoint_Pad_D1.5mm
TP37: PI_KILL; TestPoint_Pad_D1.5mm
TP38: SHORE_INHIBIT; TestPoint_Pad_D1.5mm
TP39: PIJ2_A; TestPoint_Pad_D1.5mm
TP40: PIJ2_B; TestPoint_Pad_D1.5mm
U1: PCA9555PW 0x22: LED sinks, light mode inputs; TSSOP-24_4.4x7.8mm_P0.65mm; LCSC C2864778
U2: PCA9555PW 0x23: LED sinks, the battery bar, lamp 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; TSSOP-24_4.4x7.8mm_P0.65mm; LCSC C2864778
U3: RP2040 panel controller (USB device on B16's slot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; QFN-56-1EP_7x7mm_P0.4mm_EP3.2x3.2mm; LCSC C2040
U4: W25Q16JVUXIQ 16 Mbit QSPI flash (USON-8: 1 CS 2 D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; Winbond_USON-8-1EP_3x2mm_P0.5mm_EP0.2x1.6mm; LCSC C2843335
U5: TLV75533PDBV 3.3 V 500 mA LDO for the controller,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; SOT-23-5
U6, U7, U8, U10, U11: USBLC6-2SC6; SOT-23-6; LCSC C7519
U9: 74LVC1G34 non-inverting buffer (2 A 4 Y): EMCON_H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; SOT-23-5
U_LIGHT: Vishay VEML7700 ambient light sensor (1 SCL 2 VDD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; Vishay_VEML7700; LCSC C504893
Y1: 12 MHz ABM8-272-T3 (3225): 1 XIN, 3 XOUT, 2 and 4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; Crystal_SMD_3225-4Pin_3.2x2.5mm; LCSC C20625731

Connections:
/+3V3: C2.1, C4.1, C7.1, C8.1, C9.1, C10.1, C11.1, C12.1, C13.1, C16.1, C17.1, C18.1, C25.1, C38.1, Q5.2 (S), R4.2, R7.2, R8.2, R9.2, R10.2, R11.2, R12.2, R13.2, R14.2, R16.2, R42.2, TP7.1, U1.2 (A1), U1.24 (VDD), U2.2 (A1), U2.21 (A0), U2.24 (VDD), U3.1 (IOVDD), U3.10 (IOVDD), U3.22 (IOVDD), U3.33 (IOVDD), U3.42 (IOVDD), U3.43 (ADC_AVDD), U3.44 (VREG_VIN), U3.48 (USB_VDD), U3.49 (IOVDD), U4.8 (+3V3), U5.5 (+3V3), U6.5 (VBUS), U7.5 (VBUS), U8.5 (VBUS), U9.5 (+3V3), U10.5 (VBUS), U11.5 (VBUS), U_LIGHT.2 (+3V3)
/+5V: BZ1.2 (-), C1.1, C3.1, J_PANEL.1, J_PANEL.2, SW_LIGHT.2, TP6.1, U5.1 (+5V), U5.3 (+5V)
/BAT1_A: D12.2 (A), R31.2
/BAT1_K: D12.1 (K), U2.7 (IO0_3)
/BAT2_A: D13.2 (A), R32.2
/BAT2_K: D13.1 (K), U2.8 (IO0_4)
/BAT3_A: D14.2 (A), R33.2
/BAT3_K: D14.1 (K), U2.9 (IO0_5)
/BAT4_A: D15.2 (A), R34.2
/BAT4_K: D15.1 (K), U2.10 (IO0_6)
/BAT5_A: D16.2 (A), R35.2
/BAT5_K: D16.1 (K), U2.11 (IO0_7)
/BOOT_J: JP1.1 (A), R5.2
/BZ_K: BZ1.1 (+), Q4.3 (D)
/CHG_A: D10.2 (A), R29.2
/CHG_K: D10.1 (K), U1.7 (IO0_3)
/C_DVDD: C14.1, C15.1, U3.23 (DVDD), U3.45 (VREG_VOUT), U3.50 (DVDD)
/C_RUN: R4.1, TP3.1, U3.26 (RUN)
/EMCON_HW: J_PANEL.8, TP11.1, U3.32 (GPIO21), U9.4 (EMCON_HW)
/EPD_BUSY: J_EPD.9 (BUSY_N), TP25.1, U3.9 (GPIO7)
/EPD_CS: J_EPD.12 (CSB), U3.7 (GPIO5)
/EPD_DC: J_EPD.11 (DC), U3.6 (GPIO4)
/EPD_GDR: J_EPD.2 (GDR), Q6.1 (G)
/EPD_PUMP: C31.2, D20.1 (K), D21.2 (A)
/EPD_PWR_n: Q5.1 (G), R42.1, U3.41 (GPIO29_A3)
/EPD_RESE: J_EPD.3 (RESE), Q6.2 (S), R43.1
/EPD_RST: J_EPD.10 (RST_N), U3.8 (GPIO6)
/EPD_SCL: J_EPD.13 (SCL), U3.4 (GPIO2)
/EPD_SDA: J_EPD.14 (SDA), U3.5 (GPIO3)
/EPD_SW: C31.1, D19.1 (K), L1.2, Q6.3 (D)
/EPD_VCC: C28.1, C29.1, J_EPD.15 (VDDIO), J_EPD.16 (VDD), L1.1, Q5.3 (D)
/EPD_VCOM: C37.1, J_EPD.24 (VCOM)
/EPD_VDDD: C34.1, J_EPD.18 (VDDD)
/EPD_VDH: C35.1, J_EPD.20 (VDH)
/EPD_VDHR: C33.1, J_EPD.5 (VDHR)
/EPD_VDL: C36.1, J_EPD.22 (VDL)
/EPD_VGH: C30.1, D19.2 (A), J_EPD.21 (VGH), TP26.1
/EPD_VGL: C32.1, D21.1 (K), J_EPD.23 (VGL), TP27.1
/EXP_INT: J_PANEL.6, TP9.1, U1.1 (~INT), U2.1 (~INT), U3.36 (GPIO24), U8.3 (I/O2), U8.4 (I/O2)
/GPS_A: D8.2 (A), R27.2
/GPS_K: D8.1 (K), U1.11 (IO0_7)
/HB1: J_PANEL.18, TP28.1, U3.13 (GPIO10)
/HB2: J_PANEL.19, TP29.1, U3.14 (GPIO11)
/HB3: J_PANEL.20, TP30.1, U3.15 (GPIO12)
/HDMI_SEL1: J_PANEL.12, TP34.1, U3.27 (GPIO16)
/HDMI_SEL2: J_PANEL.13, TP35.1, U3.28 (GPIO17)
/LED_RAIL: Q1.3 (D), R21.1, R22.1, R23.1, R24.1, R25.1, R26.1, R27.1, R28.1, R29.1, R30.1, R31.1, R32.1, R33.1, R34.1, R35.1, R36.1, R40.1, R41.1, TP4.1
/LED_RAIL_SW: Q1.2 (S), R15.1, R17.1, R39.1, SW_LIGHT.1, TP5.1
/LED_STAT: R6.1, U3.37 (GPIO25)
/LED_STAT_A: D18.2 (A), R6.2
/LIGHT_DAY_n: C22.1, R12.1, SW_LIGHT.5, U1.13 (IO1_0)
/LIGHT_NIGHT_n: C23.1, R13.1, SW_LIGHT.6, U1.14 (IO1_1)
/LTE_A: D7.2 (A), R26.2
/LTE_K: D7.1 (K), U1.10 (IO0_6)
/MAINRING_A: R39.2, SW_MAIN.3
/MAINSW_A: FB1.1, SW_MAIN.1
/MAINSW_A2: C26.1, FB1.2, J_MAINSW.1, U10.1 (I/O1), U10.6 (I/O1)
/MAINSW_B: FB2.1, SW_MAIN.2
/MAINSW_B2: C26.2, FB2.2, J_MAINSW.2, U10.3 (I/O2), U10.4 (I/O2)
/MCAUT_A: D2.2 (A), R22.2
/MCAUT_K: D2.1 (K), U1.6 (IO0_2)
/MESH_A: D6.2 (A), R25.2
/MESH_K: D6.1 (K), U1.9 (IO0_5)
/MSG_A: D11.2 (A), R30.2
/MSG_K: D11.1 (K), U2.5 (IO0_1)
/MWARN_A: D1.2 (A), R21.2
/MWARN_K: D1.1 (K), U1.5 (IO0_1)
/PANEL_ID: JP2.1 (A), R16.1, U1.15 (IO1_2)
/PANEL_PWM: R19.1, U3.11 (GPIO8)
/PIJ2_A: FB3.1, SW_PI.1, TP39.1
/PIJ2_A2: C27.1, FB3.2, J_PIJ2.1, U11.1 (I/O1), U11.6 (I/O1)
/PIJ2_B: FB4.1, SW_PI.2, TP40.1
/PIJ2_B2: C27.2, FB4.2, J_PIJ2.2, U11.3 (I/O2), U11.4 (I/O2)
/PIRING_A: R40.2, SW_PI.3
/PIRING_K: SW_PI.4, U2.6 (IO0_2)
/PI_KILL: J_PANEL.25, TP37.1, U3.30 (GPIO19)
/PI_SHDN_REQ: J_PANEL.24, TP36.1, U3.29 (GPIO18)
/PWM1: R44.1, U3.12 (GPIO9)
/Q1_G: Q1.1 (G), R17.2, R18.1
/Q2_D: Q2.3 (D), R18.2
/Q2_G: Q2.1 (G), R19.2, R20.1
/Q3_G: Q3.1 (G), R37.2, R38.1
/Q4_G: Q4.1 (G), R44.2, R45.1
/QSPI_D0: U3.53 (QSPI_SD0), U4.5 (QSPI_D0)
/QSPI_D1: U3.55 (QSPI_SD1), U4.2 (QSPI_D1)
/QSPI_D2: U3.54 (QSPI_SD2), U4.3 (QSPI_D2)
/QSPI_D3: U3.51 (QSPI_SD3), U4.7 (QSPI_D3)
/QSPI_SCLK: U3.52 (QSPI_SCLK), U4.6 (QSPI_SCLK)
/QSPI_SS: R5.1, U3.56 (QSPI_SS_N), U4.1 (QSPI_SS)
/RAIL_SENSE: R15.2, U3.38 (GPIO26_A0)
/SAT_A: D5.2 (A), R24.2
/SAT_K: D5.1 (K), U1.8 (IO0_4)
/SCL: J_PANEL.5, R8.1, U1.22 (SCL), U2.22 (SCL), U3.3 (GPIO1), U7.3 (I/O2), U7.4 (I/O2), U_LIGHT.1 (SCL)
/SDA: J_PANEL.4, R7.1, U1.23 (SDA), U2.23 (SDA), U3.2 (GPIO0), U7.1 (I/O1), U7.6 (I/O1), U_LIGHT.4 (SDA)
/SHORE_A: D9.2 (A), R28.2
/SHORE_INHIBIT: J_PANEL.26, TP38.1, U3.31 (GPIO20)
/SHORE_K: D9.1 (K), U2.4 (IO0_0)
/SLOT_EN1: J_PANEL.21, TP31.1, U3.16 (GPIO13)
/SLOT_EN2: J_PANEL.22, TP32.1, U3.17 (GPIO14)
/SLOT_EN3: J_PANEL.23, TP33.1, U3.18 (GPIO15)
/SOSACT_A: D4.2 (A), R23.2
/SOSACT_K: D4.1 (K), U1.4 (IO0_0)
/SOS_SW: C19.1, R9.1, SW_SOS.1, U3.40 (GPIO28_A2)
/SPARE1: TP13.1, U1.16 (IO1_3)
/SPARE2: TP14.1, U1.17 (IO1_4)
/SPARE3: TP15.1, U1.18 (IO1_5)
/SPARE4: TP16.1, U1.19 (IO1_6)
/SPARE5: TP17.1, U1.20 (IO1_7)
/SPARE6: TP18.1, U2.14 (IO1_1)
/SPARE7: TP19.1, U2.15 (IO1_2)
/SPARE8: TP20.1, U2.16 (IO1_3)
/SPARE9: TP21.1, U2.17 (IO1_4)
/SPARE10: TP22.1, U2.18 (IO1_5)
/SPARE11: TP23.1, U2.19 (IO1_6)
/SPARE12: TP24.1, U2.20 (IO1_7)
/SWCLK: TP1.1, U3.24 (SWCLK)
/SWDIO: TP2.1, U3.25 (SWD)
/TESTRING_A: R41.2, SW_TEST.3
/TEST_SW: C21.1, R11.1, SW_TEST.1, U3.39 (GPIO27_A1)
/TR_APRS: J_PANEL.7, R37.1, U3.35 (GPIO23), U8.1 (I/O1), U8.6 (I/O1)
/TX_A: D3.2 (A), R36.2
/TX_INHIBIT_n: C24.1, J_PANEL.11, R14.1, SW_EMCON.1, TP10.1, U9.2 (TX_INHIBIT_n)
/TX_K: D3.1 (K), D17.2 (A), Q3.3 (D)
/TX_LAMPTEST: D17.1 (K), U2.13 (IO1_0)
/USB_DM_R: R3.1, U3.46 (USB_DM)
/USB_DP_R: R2.1, U3.47 (USB_DP)
/USB_PNL_N: J_PANEL.16, R3.2, U6.3 (I/O2), U6.4 (I/O2)
/USB_PNL_P: J_PANEL.15, R2.2, U6.1 (I/O1), U6.6 (I/O1)
/XIN: C5.1, U3.20 (XIN), Y1.1
/XOUT: C6.1, R1.2, Y1.3
/XOUT_R: R1.1, U3.21 (XOUT)
/ZEROIZE_HW: C20.1, J_PANEL.10, R10.1, SW_ZERO.1, TP12.1, U3.34 (GPIO22)
GND: C1.2, C2.2, C3.2, C4.2, C5.2, C6.2, C7.2, C8.2, C9.2, C10.2, C11.2, C12.2, C13.2, C14.2, C15.2, C16.2, C17.2, C18.2, C19.2, C20.2, C21.2, C22.2, C23.2, C24.2, C25.2, C28.2, C29.2, C30.2, C32.2, C33.2, C34.2, C35.2, C36.2, C37.2, C38.2, D18.1 (K), D20.2 (A), H1.1, H2.1, H3.1, H4.1, H5.1, H6.1, H7.1, H8.1, JP1.2 (B), JP2.2 (B), J_EPD.8 (BS), J_EPD.17 (VSS), J_EPD.25 (SHIELD), J_EPD.26 (SHIELD), J_PANEL.3, J_PANEL.9, J_PANEL.14, J_PANEL.17, Q2.2 (S), Q3.2 (S), Q4.2 (S), R20.2, R38.2, R43.2, R45.2, SW_EMCON.2, SW_LIGHT.4, SW_MAIN.4, SW_SOS.2, SW_TEST.2, SW_TEST.4, SW_ZERO.2, TP8.1, U1.3 (A2), U1.12 (VSS), U1.21 (A0), U2.3 (A2), U2.12 (VSS), U3.19 (TESTEN), U3.57 (GND), U4.4 (GND), U4.9 (GND), U5.2 (GND), U6.2 (GND), U7.2 (GND), U8.2 (GND), U9.3 (GND), U10.2 (GND), U11.2 (GND), U_LIGHT.3 (GND), Y1.2 (G), Y1.4 (G)

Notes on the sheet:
PCB-C CONTROL PANEL BACKER C24
RIBBON FROM B16, 5 V, 3.3 V LDO, USB AND BUS ESD, FLAGS | RP2040 PANEL CONTROLLER, FLASH, CRYSTAL, BOOTSEL, BUS PULL-UPS
RIBBON FROM B16, 5 V, 3.3 V LDO, USB AND BUS ESD, FLAGS
RP2040 PANEL CONTROLLER, FLASH, CRYSTAL, BOOTSEL, BUS PULL-UPS
page 1 of 5 MeshSat field kit V2, CERN-OHL-S-2.0 PROTOTYPE, nothing built 2026-09-16
panel ribbon from B16 J_PANEL
TLV75533PDBV 3.3 V 500 mA LDO for..
RP2040 panel controller
status
BOOTSEL
p2,5
p2,4,5
p2,3,4
p3,4
p4,5
p2,4
RP2040 PANEL CONTROLLER, FLASH, CRYSTAL, BOOTSEL, BUS PULL-UPS | EXPANDERS 0x22 / 0x23, MODE INPUTS, EMCON INVERTER, STRAPS | LED RAIL, INDICATORS, TX LAMP, SWITCHES
RP2040 PANEL CONTROLLER, FLASH, CRYSTAL, BOOTSEL, BUS PULL-UPS (continued)
EXPANDERS 0x22 / 0x23, MODE INPUTS, EMCON INVERTER, STRAPS
LED RAIL, INDICATORS, TX LAMP, SWITCHES AND LEADS
page 2 of 5 MeshSat field kit V2, CERN-OHL-S-2.0 PROTOTYPE, nothing built 2026-09-16
W25Q16JVUXIQ 16 Mbit QSPI flash
12 MHz ABM8-272-T3
PCA9555PW 0x22
PANEL_ID strap
PCA9555PW 0x23
74LVC1G34 non-inverting buffer
LIGHTING DAY/NIGHT/BLACKOUT toggle..
p1,5
p1,4,5
p1,4
p1,3,4
LED RAIL, INDICATORS, TX LAMP, SWITCHES AND LEADS (continued)
page 3 of 5 MeshSat field kit V2, CERN-OHL-S-2.0 PROTOTYPE, nothing built 2026-09-16
3 mm MWARN red
3 mm MCAUT amber
3 mm SOSACT red
3 mm SAT green
3 mm MESH green
3 mm LTE green

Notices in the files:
v2/ecad/pcb-c-display-c8/pcb-c-display.kicad_sch:
page 4 of 5 MeshSat field kit V2, CERN-OHL-S-2.0 PROTOTYPE, nothing built 2026-09-16
page 5 of 5 MeshSat field kit V2, CERN-OHL-S-2.0 PROTOTYPE, nothing built 2026-09-16
